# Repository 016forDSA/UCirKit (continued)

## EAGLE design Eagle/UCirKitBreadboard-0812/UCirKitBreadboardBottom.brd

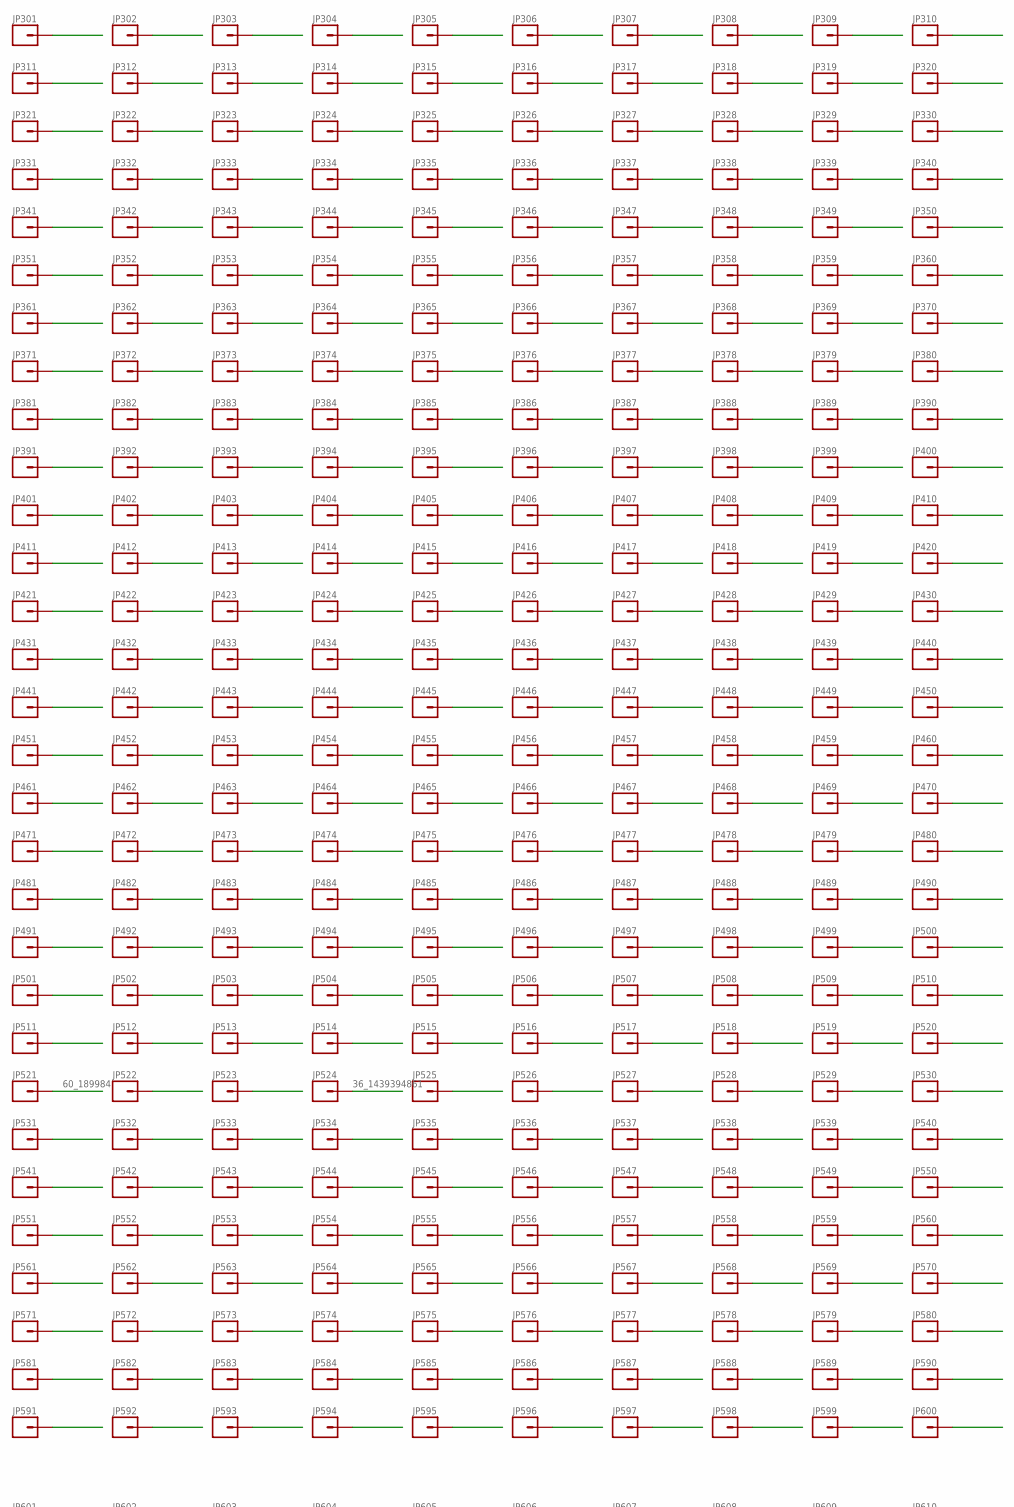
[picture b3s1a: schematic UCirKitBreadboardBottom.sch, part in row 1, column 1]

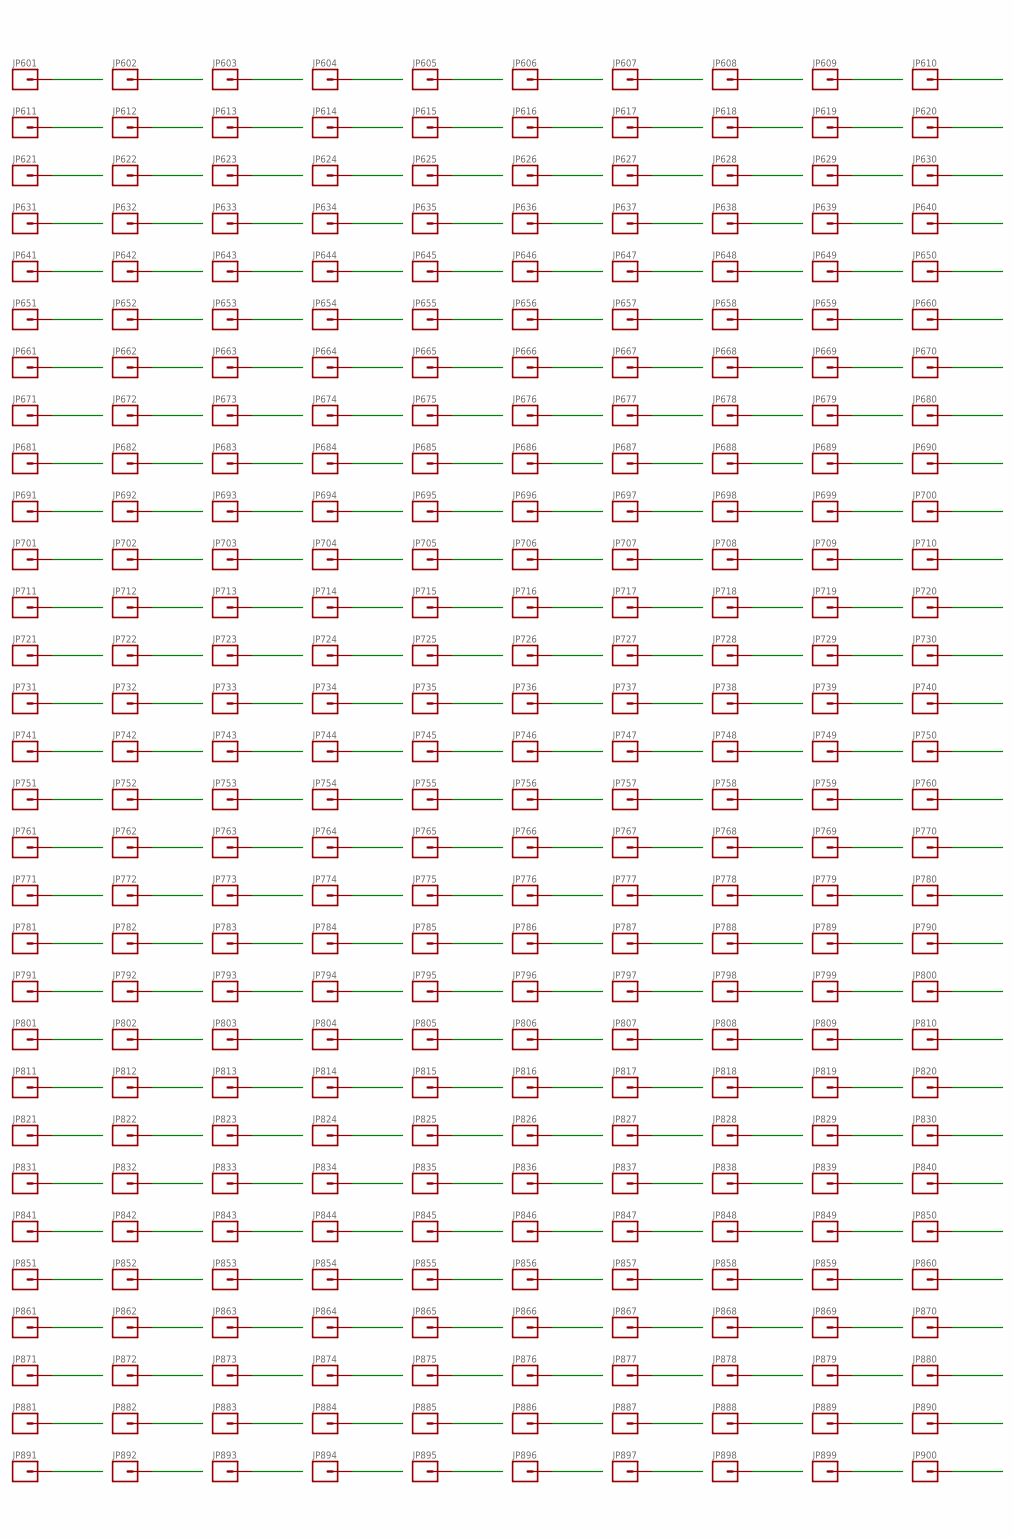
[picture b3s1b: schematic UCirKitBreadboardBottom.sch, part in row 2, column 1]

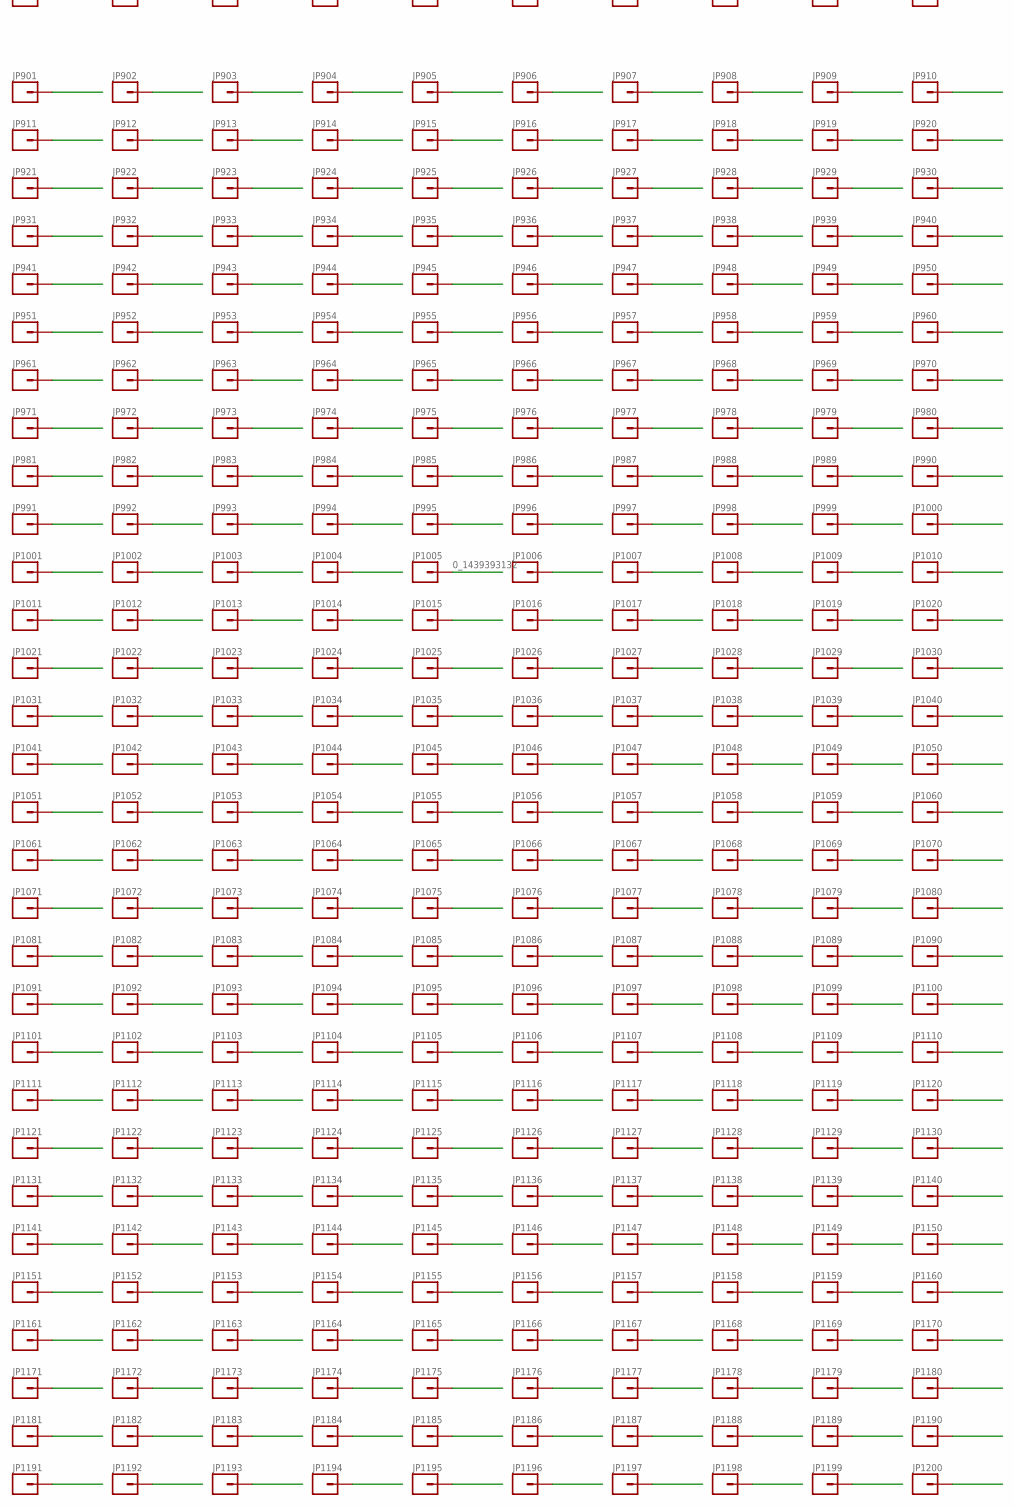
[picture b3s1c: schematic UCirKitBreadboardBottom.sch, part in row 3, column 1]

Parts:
JP301, JP302, JP303, JP304, JP305, JP306, JP307, JP308, JP309, JP310, JP311, JP312, JP313, JP314, JP315, JP316, JP317, JP318, JP319, JP320, JP321, JP322, JP323, JP324, JP325, JP326, JP327, JP328, JP329, JP330, JP331, JP332, JP333, JP334, JP335, JP336, JP337, JP338, JP339, JP340, JP341, JP342, JP343, JP344, JP345, JP346, JP347, JP348, JP349, JP350, JP351, JP352, JP353, JP354, JP355, JP356, JP357, JP358, JP359, JP360, JP361, JP362, JP363, JP364, JP365, JP366, JP367, JP368, JP369, JP370, JP371, JP372, JP373, JP374, JP375, JP376, JP377, JP378, JP379, JP380, JP381, JP382, JP383, JP384, JP385, JP386, JP387, JP388, JP389, JP390, JP391, JP392, JP393, JP394, JP395, JP396, JP397, JP398, JP399, JP400, JP401, JP402, JP403, JP404, JP405, JP406, JP407, JP408, JP409, JP410, JP411, JP412, JP413, JP414, JP415, JP416, JP417, JP418, JP419, JP420, JP421, JP422, JP423, JP424, JP425, JP426, JP427, JP428, JP429, JP430, JP431, JP432, JP433, JP434, JP435, JP436, JP437, JP438, JP439, JP440, JP441, JP442, JP443, JP444, JP445, JP446, JP447, JP448, JP449, JP450, JP451, JP452, JP453, JP454, JP455, JP456, JP457, JP458, JP459, JP460, JP461, JP462, JP463, JP464, JP465, JP466, JP467, JP468, JP469, JP470, JP471, JP472, JP473, JP474, JP475, JP476, JP477, JP478, JP479, JP480, JP481, JP482, JP483, JP484, JP485, JP486, JP487, JP488, JP489, JP490, JP491, JP492, JP493, JP494, JP495, JP496, JP497, JP498, JP499, JP500, JP501, JP502, JP503, JP504, JP505, JP506, JP507, JP508, JP509, JP510, JP511, JP512, JP513, JP514, JP515, JP516, JP517, JP518, JP519, JP520, JP521, JP522, JP523, JP524, JP525, JP526, JP527, JP528, JP529, JP530, JP531, JP532, JP533, JP534, JP535, JP536, JP537, JP538, JP539, JP540, JP541, JP542, JP543, JP544, JP545, JP546, JP547, JP548, JP549, JP550, JP551, JP552, JP553, JP554, JP555, JP556, JP557, JP558, JP559, JP560, JP561, JP562, JP563, JP564, JP565, JP566, JP567, JP568, JP569, JP570, JP571, JP572, JP573, JP574, JP575, JP576, JP577, JP578, JP579, JP580, JP581, JP582, JP583, JP584, JP585, JP586, JP587, JP588, JP589, JP590, JP591, JP592, JP593, JP594, JP595, JP596, JP597, JP598, JP599, JP600: M01PTH_SMD_2.18X1.0668MM_NO_SILK; 1X01_SMD_2.18X1.0668MM_NO_SILK
JP601, JP602, JP603, JP604, JP605, JP606, JP607, JP608, JP609, JP610, JP611, JP612, JP613, JP614, JP615, JP616, JP617, JP618, JP619, JP620, JP621, JP622, JP623, JP624, JP625, JP626, JP627, JP628, JP629, JP630, JP631, JP632, JP633, JP634, JP635, JP636, JP637, JP638, JP639, JP640, JP641, JP642, JP643, JP644, JP645, JP646, JP647, JP648, JP649, JP650, JP651, JP652, JP653, JP654, JP655, JP656, JP657, JP658, JP659, JP660, JP661, JP662, JP663, JP664, JP665, JP666, JP667, JP668, JP669, JP670, JP671, JP672, JP673, JP674, JP675, JP676, JP677, JP678, JP679, JP680, JP681, JP682, JP683, JP684, JP685, JP686, JP687, JP688, JP689, JP690, JP691, JP692, JP693, JP694, JP695, JP696, JP697, JP698, JP699, JP700, JP701, JP702, JP703, JP704, JP705, JP706, JP707, JP708, JP709, JP710, JP711, JP712, JP713, JP714, JP715, JP716, JP717, JP718, JP719, JP720, JP721, JP722, JP723, JP724, JP725, JP726, JP727, JP728, JP729, JP730, JP731, JP732, JP733, JP734, JP735, JP736, JP737, JP738, JP739, JP740, JP741, JP742, JP743, JP744, JP745, JP746, JP747, JP748, JP749, JP750, JP751, JP752, JP753, JP754, JP755, JP756, JP757, JP758, JP759, JP760, JP761, JP762, JP763, JP764, JP765, JP766, JP767, JP768, JP769, JP770, JP771, JP772, JP773, JP774, JP775, JP776, JP777, JP778, JP779, JP780, JP781, JP782, JP783, JP784, JP785, JP786, JP787, JP788, JP789, JP790, JP791, JP792, JP793, JP794, JP795, JP796, JP797, JP798, JP799, JP800, JP801, JP802, JP803, JP804, JP805, JP806, JP807, JP808, JP809, JP810, JP811, JP812, JP813, JP814, JP815, JP816, JP817, JP818, JP819, JP820, JP821, JP822, JP823, JP824, JP825, JP826, JP827, JP828, JP829, JP830, JP831, JP832, JP833, JP834, JP835, JP836, JP837, JP838, JP839, JP840, JP841, JP842, JP843, JP844, JP845, JP846, JP847, JP848, JP849, JP850, JP851, JP852, JP853, JP854, JP855, JP856, JP857, JP858, JP859, JP860, JP861, JP862, JP863, JP864, JP865, JP866, JP867, JP868, JP869, JP870, JP871, JP872, JP873, JP874, JP875, JP876, JP877, JP878, JP879, JP880, JP881, JP882, JP883, JP884, JP885, JP886, JP887, JP888, JP889, JP890, JP891, JP892, JP893, JP894, JP895, JP896, JP897, JP898, JP899, JP900, JP901, JP902, JP903, JP904, JP905, JP906, JP907, JP908, JP909, JP910, JP911, JP912, JP913, JP914, JP915, JP916, JP917, JP918, JP919, JP920, JP921, JP922, JP923, JP924, JP925, JP926, JP927, JP928, JP929, JP930, JP931, JP932, JP933, JP934, JP935, JP936, JP937, JP938, JP939, JP940, JP941, JP942, JP943, JP944, JP945, JP946, JP947, JP948, JP949, JP950, JP951, JP952, JP953, JP954, JP955, JP956, JP957, JP958, JP959, JP960, JP961, JP962, JP963, JP964, JP965, JP966, JP967, JP968, JP969, JP970, JP971, JP972, JP973, JP974, JP975, JP976, JP977, JP978, JP979, JP980, JP981, JP982, JP983, JP984, JP985, JP986, JP987, JP988, JP989, JP990, JP991, JP992, JP993, JP994, JP995, JP996, JP997, JP998, JP999, JP1000, JP1001, JP1002, JP1003, JP1004, JP1005, JP1006, JP1007, JP1008, JP1009, JP1010, JP1011, JP1012, JP1013, JP1014, JP1015, JP1016, JP1017, JP1018, JP1019, JP1020, JP1021, JP1022, JP1023, JP1024, JP1025, JP1026, JP1027, JP1028, JP1029, JP1030, JP1031, JP1032, JP1033, JP1034, JP1035, JP1036, JP1037, JP1038, JP1039, JP1040, JP1041, JP1042, JP1043, JP1044, JP1045, JP1046, JP1047, JP1048, JP1049, JP1050, JP1051, JP1052, JP1053, JP1054, JP1055, JP1056, JP1057, JP1058, JP1059, JP1060, JP1061, JP1062, JP1063, JP1064, JP1065, JP1066, JP1067, JP1068, JP1069, JP1070, JP1071, JP1072, JP1073, JP1074, JP1075, JP1076, JP1077, JP1078, JP1079, JP1080, JP1081, JP1082, JP1083, JP1084, JP1085, JP1086, JP1087, JP1088, JP1089, JP1090, JP1091, JP1092, JP1093, JP1094, JP1095, JP1096, JP1097, JP1098, JP1099, JP1100, JP1101, JP1102, JP1103, JP1104, JP1105, JP1106, JP1107, JP1108, JP1109, JP1110, JP1111, JP1112, JP1113, JP1114, JP1115, JP1116, JP1117, JP1118, JP1119, JP1120, JP1121, JP1122, JP1123, JP1124, JP1125, JP1126, JP1127, JP1128, JP1129, JP1130, JP1131, JP1132, JP1133, JP1134, JP1135, JP1136, JP1137, JP1138, JP1139, JP1140, JP1141, JP1142, JP1143, JP1144, JP1145, JP1146, JP1147, JP1148, JP1149, JP1150, JP1151, JP1152, JP1153, JP1154, JP1155, JP1156, JP1157, JP1158, JP1159, JP1160, JP1161, JP1162, JP1163, JP1164, JP1165, JP1166, JP1167, JP1168, JP1169, JP1170, JP1171, JP1172, JP1173, JP1174, JP1175, JP1176, JP1177, JP1178, JP1179, JP1180, JP1181, JP1182, JP1183, JP1184, JP1185, JP1186, JP1187, JP1188, JP1189, JP1190, JP1191, JP1192, JP1193, JP1194, JP1195, JP1196, JP1197, JP1198, JP1199, JP1200: M01PTH_SMD_1.27X0.635MM_NO_SILK; 1X01_SMD_1.27X0.635MM_NO_SILK

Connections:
0_1439393083: JP591.P$2, JP719.P$2, JP1019.P$2
0_1439393096: JP581.P$2, JP717.P$2, JP1017.P$2
0_1439393111: JP571.P$2, JP715.P$2, JP1015.P$2
0_1439393132: JP705.P$2, JP1005.P$2
0_1439393222: JP561.P$2, JP713.P$2, JP1013.P$2
0_1439393235: JP551.P$2, JP711.P$2, JP1011.P$2
0_1439393247: JP541.P$2, JP709.P$2, JP1009.P$2
0_1439393259: JP531.P$2, JP707.P$2, JP1007.P$2
0_1439393301: JP706.P$2, JP1006.P$2
0_1439393535: JP511.P$2, JP703.P$2, JP1003.P$2
0_1439393546: JP501.P$2, JP701.P$2, JP1001.P$2
0_1439393557: JP491.P$2, JP699.P$2, JP999.P$2
0_1439393568: JP481.P$2, JP697.P$2, JP997.P$2
0_1439393578: JP471.P$2, JP695.P$2, JP995.P$2
0_1439393590: JP461.P$2, JP693.P$2, JP993.P$2
0_1439393601: JP451.P$2, JP691.P$2, JP991.P$2
0_1439393611: JP441.P$2, JP689.P$2, JP989.P$2
0_1439393621: JP431.P$2, JP687.P$2, JP987.P$2
0_1439393632: JP421.P$2, JP685.P$2, JP985.P$2
0_1439393643: JP411.P$2, JP683.P$2, JP983.P$2
0_1439393653: JP401.P$2, JP681.P$2, JP981.P$2
0_1439393662: JP391.P$2, JP679.P$2, JP979.P$2
0_1439393672: JP381.P$2, JP677.P$2, JP977.P$2
0_1439393682: JP371.P$2, JP675.P$2, JP975.P$2
0_1439393692: JP361.P$2, JP673.P$2, JP973.P$2
0_1439393702: JP351.P$2, JP671.P$2, JP971.P$2
0_1439393713: JP341.P$2, JP669.P$2, JP969.P$2
0_1439393723: JP331.P$2, JP667.P$2, JP967.P$2
0_1439393733: JP321.P$2, JP665.P$2, JP965.P$2
0_1439393743: JP311.P$2, JP663.P$2, JP963.P$2
0_1439393751: JP301.P$2, JP662.P$2, JP962.P$2
0_1439394322: JP303.P$2, JP841.P$2, JP1141.P$2
0_1439394368: JP310.P$2, JP721.P$2, JP1021.P$2
0_1439394379: JP320.P$2, JP723.P$2, JP1023.P$2
0_1439394391: JP330.P$2, JP725.P$2, JP1025.P$2
0_1439394441: JP340.P$2, JP727.P$2, JP1027.P$2
0_1439394451: JP350.P$2, JP729.P$2, JP1029.P$2
0_1439394459: JP360.P$2, JP731.P$2, JP1031.P$2
0_1439394467: JP370.P$2, JP733.P$2, JP1033.P$2
0_1439394476: JP380.P$2, JP735.P$2, JP1035.P$2
0_1439394485: JP390.P$2, JP737.P$2, JP1037.P$2
0_1439394493: JP400.P$2, JP739.P$2, JP1039.P$2
0_1439394502: JP410.P$2, JP741.P$2, JP1041.P$2
0_1439394512: JP420.P$2, JP743.P$2, JP1043.P$2
0_1439394521: JP430.P$2, JP745.P$2, JP1045.P$2
0_1439394528: JP440.P$2, JP747.P$2, JP1047.P$2
0_1439394536: JP450.P$2, JP749.P$2, JP1049.P$2
0_1439394545: JP460.P$2, JP751.P$2, JP1051.P$2
0_1439394554: JP470.P$2, JP753.P$2, JP1053.P$2
0_1439394565: JP480.P$2, JP755.P$2, JP1055.P$2
0_1439394575: JP490.P$2, JP757.P$2, JP1057.P$2
0_1439394583: JP500.P$2, JP759.P$2, JP1059.P$2
0_1439394592: JP510.P$2, JP761.P$2, JP1061.P$2
0_1439394601: JP520.P$2, JP763.P$2, JP1063.P$2
0_1439394609: JP530.P$2, JP765.P$2, JP1065.P$2
0_1439394617: JP540.P$2, JP767.P$2, JP1067.P$2
0_1439394705: JP550.P$2, JP769.P$2, JP1069.P$2
0_1439394717: JP560.P$2, JP771.P$2, JP1071.P$2
0_1439394727: JP570.P$2, JP773.P$2, JP1073.P$2
0_1439394736: JP580.P$2, JP775.P$2, JP1075.P$2
0_1439394745: JP590.P$2, JP777.P$2, JP1077.P$2
0_1439394755: JP600.P$2, JP779.P$2, JP1079.P$2
0_1439394769: JP593.P$2, JP881.P$2, JP1181.P$2
0_1439394798: JP306.P$2, JP861.P$2, JP1161.P$2
0_1439394824: JP596.P$2, JP891.P$2, JP1191.P$2
0_1439394861: JP363.P$2, JP602.P$2, JP902.P$2
0_1439394997: JP378.P$2, JP781.P$2, JP1081.P$2
1_1439393083: JP592.P$2, JP720.P$2, JP1020.P$2
1_1439393096: JP582.P$2, JP718.P$2, JP1018.P$2
1_1439393111: JP572.P$2, JP716.P$2, JP1016.P$2
1_1439393222: JP562.P$2, JP714.P$2, JP1014.P$2
1_1439393235: JP552.P$2, JP712.P$2, JP1012.P$2
1_1439393247: JP542.P$2, JP710.P$2, JP1010.P$2
1_1439393259: JP532.P$2, JP708.P$2, JP1008.P$2
1_1439393535: JP512.P$2, JP704.P$2, JP1004.P$2
1_1439393546: JP502.P$2, JP702.P$2, JP1002.P$2
1_1439393557: JP492.P$2, JP700.P$2, JP1000.P$2
1_1439393568: JP482.P$2, JP698.P$2, JP998.P$2
1_1439393578: JP472.P$2, JP696.P$2, JP996.P$2
1_1439393590: JP462.P$2, JP694.P$2, JP994.P$2
1_1439393601: JP452.P$2, JP692.P$2, JP992.P$2
1_1439393611: JP442.P$2, JP690.P$2, JP990.P$2
1_1439393621: JP432.P$2, JP688.P$2, JP988.P$2
1_1439393632: JP422.P$2, JP686.P$2, JP986.P$2
1_1439393643: JP412.P$2, JP684.P$2, JP984.P$2
1_1439393653: JP402.P$2, JP682.P$2, JP982.P$2
1_1439393662: JP392.P$2, JP680.P$2, JP980.P$2
1_1439393672: JP382.P$2, JP678.P$2, JP978.P$2
1_1439393682: JP372.P$2, JP676.P$2, JP976.P$2
1_1439393692: JP362.P$2, JP674.P$2, JP974.P$2
1_1439393702: JP352.P$2, JP672.P$2, JP972.P$2
1_1439393713: JP342.P$2, JP670.P$2, JP970.P$2
1_1439393723: JP332.P$2, JP668.P$2, JP968.P$2
1_1439393733: JP322.P$2, JP666.P$2, JP966.P$2
1_1439393743: JP312.P$2, JP664.P$2, JP964.P$2
1_1439394322: JP304.P$2, JP842.P$2, JP1142.P$2
1_1439394368: JP309.P$2, JP722.P$2, JP1022.P$2
1_1439394379: JP319.P$2, JP724.P$2, JP1024.P$2
1_1439394391: JP329.P$2, JP726.P$2, JP1026.P$2
1_1439394441: JP339.P$2, JP728.P$2, JP1028.P$2
1_1439394451: JP349.P$2, JP730.P$2, JP1030.P$2
1_1439394459: JP359.P$2, JP732.P$2, JP1032.P$2
1_1439394467: JP369.P$2, JP734.P$2, JP1034.P$2
1_1439394476: JP379.P$2, JP736.P$2, JP1036.P$2
1_1439394485: JP389.P$2, JP738.P$2, JP1038.P$2
1_1439394493: JP399.P$2, JP740.P$2, JP1040.P$2
1_1439394502: JP409.P$2, JP742.P$2, JP1042.P$2
1_1439394512: JP419.P$2, JP744.P$2, JP1044.P$2
1_1439394521: JP429.P$2, JP746.P$2, JP1046.P$2
1_1439394528: JP439.P$2, JP748.P$2, JP1048.P$2
1_1439394536: JP449.P$2, JP750.P$2, JP1050.P$2
1_1439394545: JP459.P$2, JP752.P$2, JP1052.P$2
1_1439394554: JP469.P$2, JP754.P$2, JP1054.P$2
1_1439394565: JP479.P$2, JP756.P$2, JP1056.P$2
1_1439394575: JP489.P$2, JP758.P$2, JP1058.P$2
1_1439394583: JP499.P$2, JP760.P$2, JP1060.P$2
1_1439394592: JP509.P$2, JP762.P$2, JP1062.P$2
1_1439394601: JP519.P$2, JP764.P$2, JP1064.P$2
1_1439394609: JP529.P$2, JP766.P$2, JP1066.P$2
1_1439394617: JP539.P$2, JP768.P$2, JP1068.P$2
1_1439394705: JP549.P$2, JP770.P$2, JP1070.P$2
1_1439394717: JP559.P$2, JP772.P$2, JP1072.P$2
1_1439394727: JP569.P$2, JP774.P$2, JP1074.P$2
1_1439394736: JP579.P$2, JP776.P$2, JP1076.P$2
1_1439394745: JP589.P$2, JP778.P$2, JP1078.P$2
1_1439394755: JP599.P$2, JP780.P$2, JP1080.P$2
1_1439394769: JP594.P$2, JP882.P$2, JP1182.P$2
1_1439394798: JP307.P$2, JP862.P$2, JP1162.P$2
1_1439394824: JP597.P$2, JP892.P$2, JP1192.P$2
1_1439394861: JP373.P$2, JP603.P$2, JP903.P$2
1_1439394997: JP377.P$2, JP782.P$2, JP1082.P$2
2_1439394322: JP313.P$2, JP843.P$2, JP1143.P$2
2_1439394769: JP583.P$2, JP883.P$2, JP1183.P$2
2_1439394798: JP308.P$2, JP863.P$2, JP1163.P$2
2_1439394824: JP598.P$2, JP893.P$2, JP1193.P$2
2_1439394861: JP383.P$2, JP604.P$2, JP904.P$2
2_1439394997: JP388.P$2, JP783.P$2, JP1083.P$2
3_1439394322: JP305.P$2, JP844.P$2, JP1144.P$2
3_1439394769: JP595.P$2, JP884.P$2, JP1184.P$2
3_1439394798: JP317.P$2, JP864.P$2, JP1164.P$2
3_1439394824: JP587.P$2, JP894.P$2, JP1194.P$2
3_1439394861: JP374.P$2, JP605.P$2, JP905.P$2
3_1439394997: JP366.P$2, JP784.P$2, JP1084.P$2
4_1439394322: JP314.P$2, JP845.P$2, JP1145.P$2
4_1439394769: JP584.P$2, JP885.P$2, JP1185.P$2
4_1439394798: JP318.P$2, JP865.P$2, JP1165.P$2
4_1439394824: JP588.P$2, JP895.P$2, JP1195.P$2
4_1439394861: JP393.P$2, JP606.P$2, JP906.P$2
4_1439394997: JP387.P$2, JP785.P$2, JP1085.P$2
5_1439394322: JP315.P$2, JP846.P$2, JP1146.P$2
5_1439394769: JP585.P$2, JP886.P$2, JP1186.P$2
5_1439394798: JP316.P$2, JP866.P$2, JP1166.P$2
5_1439394824: JP586.P$2, JP896.P$2, JP1196.P$2
5_1439394861: JP384.P$2, JP607.P$2, JP907.P$2
5_1439394997: JP398.P$2, JP786.P$2, JP1086.P$2
6_1439394322: JP324.P$2, JP847.P$2, JP1147.P$2
6_1439394769: JP574.P$2, JP887.P$2, JP1187.P$2
6_1439394798: JP328.P$2, JP867.P$2, JP1167.P$2
6_1439394824: JP578.P$2, JP897.P$2, JP1197.P$2
6_1439394861: JP375.P$2, JP608.P$2, JP908.P$2
6_1439394997: JP376.P$2, JP787.P$2, JP1087.P$2
7_1439394322: JP325.P$2, JP848.P$2, JP1148.P$2
7_1439394769: JP575.P$2, JP888.P$2, JP1188.P$2
7_1439394798: JP327.P$2, JP868.P$2, JP1168.P$2
7_1439394824: JP577.P$2, JP898.P$2, JP1198.P$2
7_1439394861: JP403.P$2, JP609.P$2, JP909.P$2
7_1439394997: JP408.P$2, JP788.P$2, JP1088.P$2
8_1439394322: JP323.P$2, JP849.P$2, JP1149.P$2
8_1439394769: JP573.P$2, JP889.P$2, JP1189.P$2
8_1439394798: JP326.P$2, JP869.P$2, JP1169.P$2
8_1439394824: JP568.P$2, JP899.P$2, JP1199.P$2
8_1439394861: JP394.P$2, JP610.P$2, JP910.P$2
8_1439394997: JP397.P$2, JP789.P$2, JP1089.P$2
9_1439394322: JP335.P$2, JP850.P$2, JP1150.P$2
9_1439394769: JP565.P$2, JP890.P$2, JP1190.P$2
9_1439394798: JP338.P$2, JP870.P$2, JP1170.P$2
9_1439394824: JP576.P$2, JP900.P$2, JP1200.P$2
9_1439394861: JP385.P$2, JP611.P$2, JP911.P$2
9_1439394997: JP386.P$2, JP790.P$2, JP1090.P$2
10_1439394322: JP333.P$2, JP851.P$2, JP1151.P$2
10_1439394798: JP336.P$2, JP871.P$2, JP1171.P$2
10_1439394861: JP413.P$2, JP612.P$2, JP912.P$2
10_1439394997: JP418.P$2, JP791.P$2, JP1091.P$2
11_1439394322: JP334.P$2, JP852.P$2, JP1152.P$2
11_1439394798: JP337.P$2, JP872.P$2, JP1172.P$2
11_1439394861: JP404.P$2, JP613.P$2, JP913.P$2
11_1439394997: JP407.P$2, JP792.P$2, JP1092.P$2
12_1439394322: JP343.P$2, JP853.P$2, JP1153.P$2
12_1439394798: JP347.P$2, JP873.P$2, JP1173.P$2
12_1439394861: JP423.P$2, JP614.P$2, JP914.P$2
12_1439394997: JP396.P$2, JP793.P$2, JP1093.P$2
13_1439394322: JP344.P$2, JP854.P$2, JP1154.P$2
13_1439394798: JP348.P$2, JP874.P$2, JP1174.P$2
13_1439394861: JP414.P$2, JP615.P$2, JP915.P$2
13_1439394997: JP428.P$2, JP794.P$2, JP1094.P$2
14_1439394322: JP345.P$2, JP855.P$2, JP1155.P$2
14_1439394798: JP346.P$2, JP875.P$2, JP1175.P$2
14_1439394861: JP395.P$2, JP616.P$2, JP916.P$2
14_1439394997: JP417.P$2, JP795.P$2, JP1095.P$2
15_1439394322: JP353.P$2, JP856.P$2, JP1156.P$2
15_1439394798: JP358.P$2, JP876.P$2, JP1176.P$2
15_1439394861: JP433.P$2, JP617.P$2, JP917.P$2
15_1439394997: JP438.P$2, JP796.P$2, JP1096.P$2
16_1439394322: JP354.P$2, JP857.P$2, JP1157.P$2
16_1439394798: JP357.P$2, JP877.P$2, JP1177.P$2
16_1439394861: JP424.P$2, JP618.P$2, JP918.P$2
16_1439394997: JP427.P$2, JP797.P$2, JP1097.P$2
17_1439394322: JP355.P$2, JP858.P$2, JP1158.P$2
17_1439394798: JP356.P$2, JP878.P$2, JP1178.P$2
17_1439394861: JP443.P$2, JP619.P$2, JP919.P$2
17_1439394997: JP406.P$2, JP798.P$2, JP1098.P$2
18_1439394322: JP365.P$2, JP859.P$2, JP1159.P$2
18_1439394798: JP368.P$2, JP879.P$2, JP1179.P$2
18_1439394861: JP434.P$2, JP620.P$2, JP920.P$2
18_1439394997: JP448.P$2, JP799.P$2, JP1099.P$2
19_1439394322: JP364.P$2, JP860.P$2, JP1160.P$2
19_1439394798: JP367.P$2, JP880.P$2, JP1180.P$2
19_1439394861: JP453.P$2, JP621.P$2, JP921.P$2
19_1439394997: JP437.P$2, JP800.P$2, JP1100.P$2
20_1439394861: JP444.P$2, JP622.P$2, JP922.P$2
20_1439394997: JP458.P$2, JP801.P$2, JP1101.P$2
21_1439394861: JP463.P$2, JP623.P$2, JP923.P$2
21_1439394997: JP447.P$2, JP802.P$2, JP1102.P$2
22_1439394861: JP454.P$2, JP624.P$2, JP924.P$2
22_1439394997: JP416.P$2, JP803.P$2, JP1103.P$2
23_1439394861: JP473.P$2, JP625.P$2, JP925.P$2
23_1439394997: JP468.P$2, JP804.P$2, JP1104.P$2
24_1439394861: JP464.P$2, JP626.P$2, JP926.P$2
24_1439394997: JP457.P$2, JP805.P$2, JP1105.P$2
25_1439394861: JP483.P$2, JP627.P$2, JP927.P$2
25_1439394997: JP478.P$2, JP806.P$2, JP1106.P$2
26_1439394861: JP474.P$2, JP628.P$2, JP928.P$2
26_1439394997: JP467.P$2, JP807.P$2, JP1107.P$2
27_1439394861: JP493.P$2, JP629.P$2, JP929.P$2
27_1439394997: JP488.P$2, JP808.P$2, JP1108.P$2
28_1439394861: JP484.P$2, JP630.P$2, JP930.P$2
28_1439394997: JP477.P$2, JP809.P$2, JP1109.P$2
29_1439394861: JP503.P$2, JP631.P$2, JP931.P$2
29_1439394997: JP498.P$2, JP810.P$2, JP1110.P$2
30_1439394861: JP494.P$2, JP632.P$2, JP932.P$2
30_1439394997: JP487.P$2, JP811.P$2, JP1111.P$2
31_1439394861: JP513.P$2, JP633.P$2, JP933.P$2
31_1439394997: JP508.P$2, JP812.P$2, JP1112.P$2
32_1439394861: JP504.P$2, JP634.P$2, JP934.P$2
32_1439394997: JP497.P$2, JP813.P$2, JP1113.P$2
33_1439394861: JP523.P$2, JP635.P$2, JP935.P$2
33_1439394997: JP518.P$2, JP814.P$2, JP1114.P$2
34_1439394861: JP514.P$2, JP636.P$2, JP936.P$2
34_1439394997: JP507.P$2, JP815.P$2, JP1115.P$2
35_1439394861: JP533.P$2, JP637.P$2, JP937.P$2
35_1439394997: JP528.P$2, JP816.P$2, JP1116.P$2
36_1439394861: JP524.P$2, JP638.P$2, JP938.P$2
36_1439394997: JP517.P$2, JP817.P$2, JP1117.P$2
37_1439394861: JP543.P$2, JP639.P$2, JP939.P$2
37_1439394997: JP538.P$2, JP818.P$2, JP1118.P$2
38_1439394861: JP534.P$2, JP640.P$2, JP940.P$2
38_1439394997: JP527.P$2, JP819.P$2, JP1119.P$2
39_1439394861: JP553.P$2, JP641.P$2, JP941.P$2
39_1439394997: JP548.P$2, JP820.P$2, JP1120.P$2
40_1439394861: JP544.P$2, JP642.P$2, JP942.P$2
40_1439394997: JP537.P$2, JP821.P$2, JP1121.P$2
41_1439394861: JP563.P$2, JP643.P$2, JP943.P$2
41_1439394997: JP558.P$2, JP822.P$2, JP1122.P$2
42_1439394861: JP554.P$2, JP644.P$2, JP944.P$2
42_1439394997: JP547.P$2, JP823.P$2, JP1123.P$2
43_1439394861: JP525.P$2, JP645.P$2, JP945.P$2
43_1439394997: JP557.P$2, JP824.P$2, JP1124.P$2
44_1439394861: JP564.P$2, JP646.P$2, JP946.P$2
44_1439394997: JP526.P$2, JP825.P$2, JP1125.P$2
45_1439394861: JP535.P$2, JP647.P$2, JP947.P$2
45_1439394997: JP567.P$2, JP826.P$2, JP1126.P$2
46_1439394861: JP545.P$2, JP648.P$2, JP948.P$2
46_1439394997: JP536.P$2, JP827.P$2, JP1127.P$2
47_1439394861: JP555.P$2, JP649.P$2, JP949.P$2
47_1439394997: JP546.P$2, JP828.P$2, JP1128.P$2
48_1439394861: JP515.P$2, JP650.P$2, JP950.P$2
48_1439394997: JP556.P$2, JP829.P$2, JP1129.P$2
49_1439394861: JP505.P$2, JP651.P$2, JP951.P$2
49_1439394997: JP566.P$2, JP830.P$2, JP1130.P$2
50_1439394861: JP495.P$2, JP652.P$2, JP952.P$2
50_1439394997: JP516.P$2, JP831.P$2, JP1131.P$2
51_1439394861: JP485.P$2, JP653.P$2, JP953.P$2
51_1439394997: JP506.P$2, JP832.P$2, JP1132.P$2
52_1439394861: JP475.P$2, JP654.P$2, JP954.P$2
52_1439394997: JP496.P$2, JP833.P$2, JP1133.P$2
53_1439394861: JP465.P$2, JP655.P$2, JP955.P$2
53_1439394997: JP486.P$2, JP834.P$2, JP1134.P$2
54_1439394861: JP455.P$2, JP656.P$2, JP956.P$2
54_1439394997: JP476.P$2, JP835.P$2, JP1135.P$2
55_1439394861: JP445.P$2, JP657.P$2, JP957.P$2
55_1439394997: JP466.P$2, JP836.P$2, JP1136.P$2
56_1439394861: JP435.P$2, JP658.P$2, JP958.P$2
56_1439394997: JP456.P$2, JP837.P$2, JP1137.P$2
57_1439394861: JP425.P$2, JP659.P$2, JP959.P$2
57_1439394997: JP446.P$2, JP838.P$2, JP1138.P$2
58_1439394861: JP415.P$2, JP660.P$2, JP960.P$2
58_1439394997: JP436.P$2, JP839.P$2, JP1139.P$2
59_1439394997: JP426.P$2, JP840.P$2, JP1140.P$2
60_19999: JP302.P$2, JP661.P$2, JP961.P$2
60_029414: JP405.P$2, JP601.P$2, JP901.P$2
60_172194: JP522.P$2
60_189984: JP521.P$2

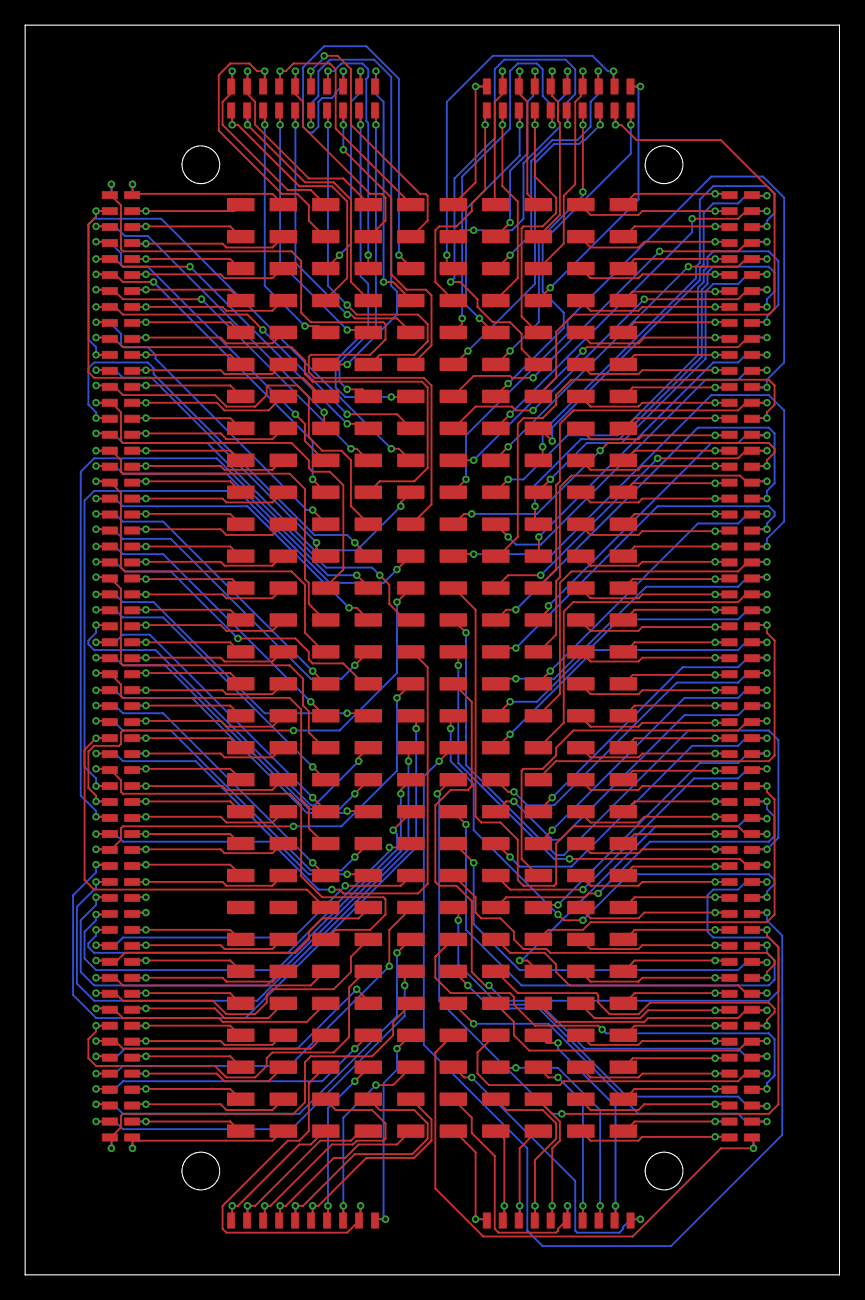
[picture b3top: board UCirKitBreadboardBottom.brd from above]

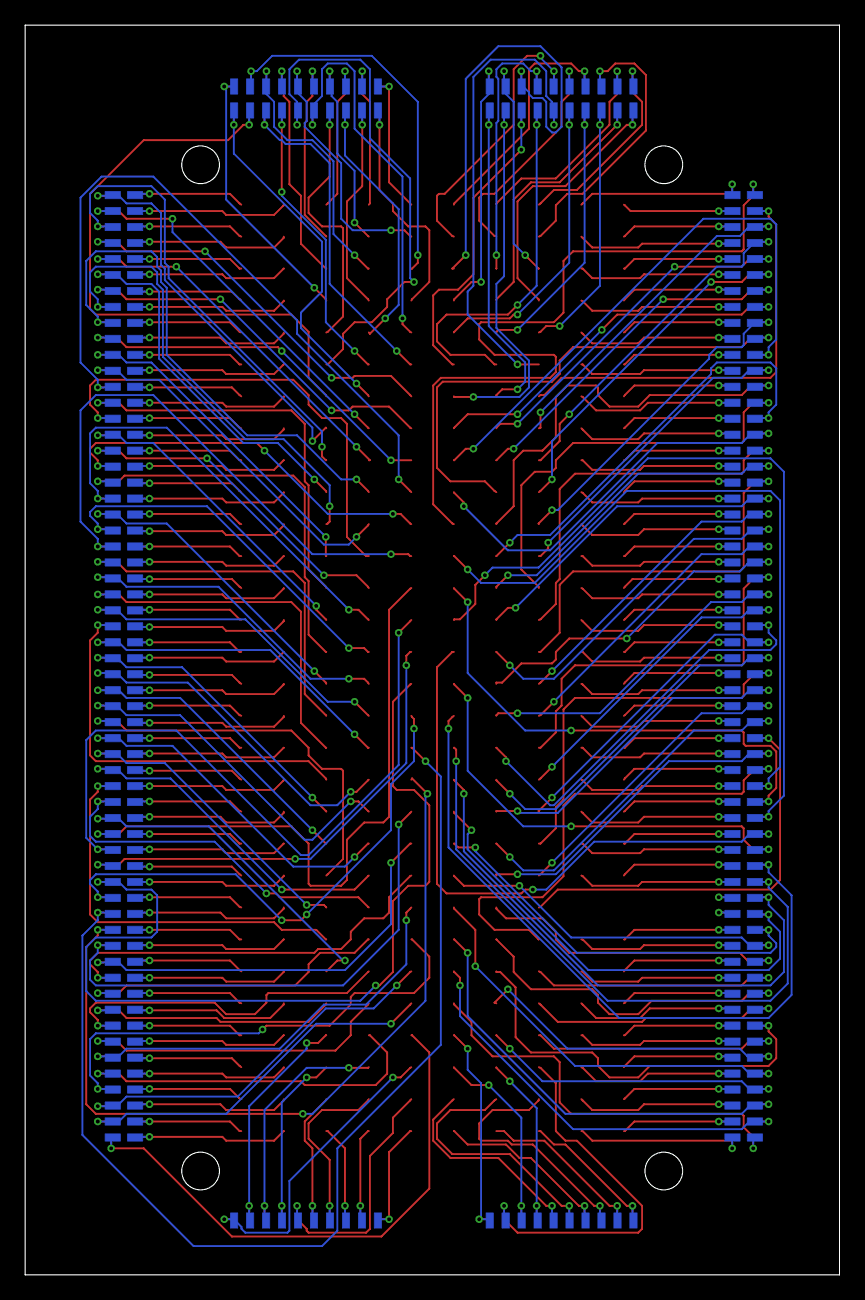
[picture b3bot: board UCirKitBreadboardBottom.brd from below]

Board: 2 copper layers, 64.8 x 99.4 mm, 900 parts (300 on the bottom side), 300 nets.
